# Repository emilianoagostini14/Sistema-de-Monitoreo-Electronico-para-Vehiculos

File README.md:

# Sistema-de-Monitoreo-Electronico-para-Vehiculos
Este repositorio contendrá los programas, archivos y diseños del proyecto integrador Sistema de Monitoreo Electronico  para Vehiculos

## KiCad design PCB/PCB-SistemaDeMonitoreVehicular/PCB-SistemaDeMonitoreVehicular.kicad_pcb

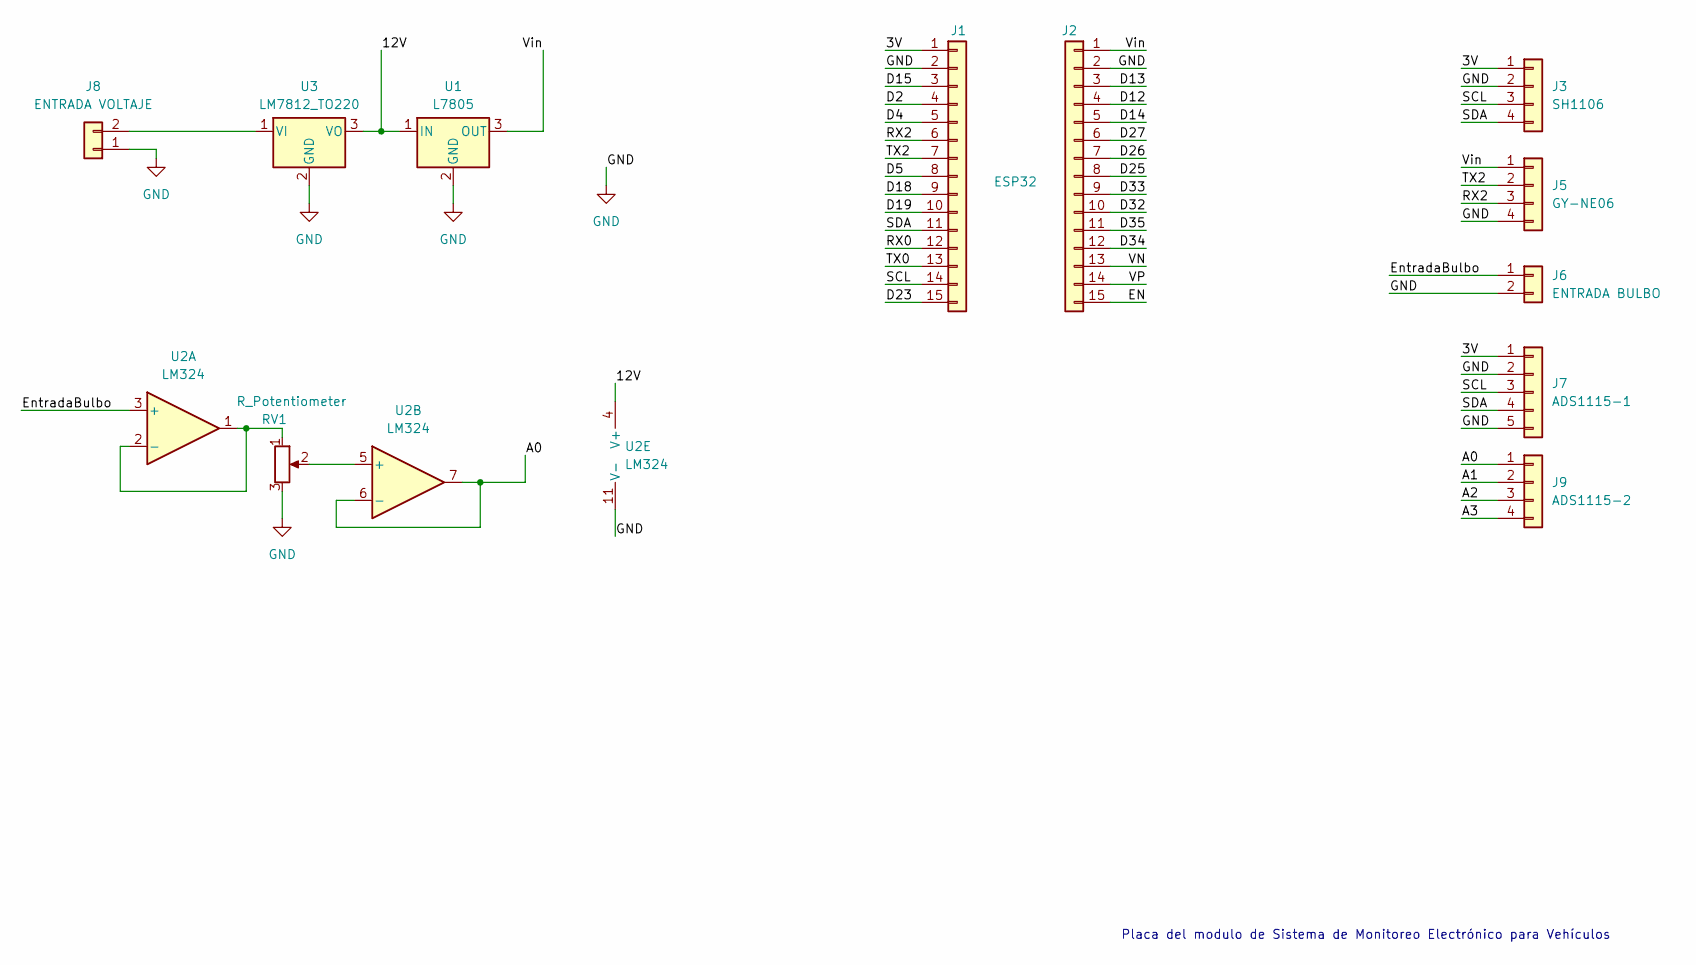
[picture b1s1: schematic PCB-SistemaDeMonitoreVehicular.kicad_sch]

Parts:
J1: ESP32; PinHeader_1x15_P2.54mm_Vertical
J2: Conn_01x15; PinHeader_1x15_P2.54mm_Vertical
J3: SH1106; PinHeader_1x04_P2.54mm_Vertical
J5: GY-NE06; PinHeader_1x04_P2.54mm_Vertical
J6: ENTRADA BULBO; TerminalBlock_bornier-2_P5.08mm
J7: ADS1115-1; PinHeader_1x05_P2.54mm_Vertical
J8: ENTRADA VOLTAJE; TerminalBlock_bornier-2_P5.08mm
J9: ADS1115-2; PinHeader_1x04_P2.54mm_Vertical
RV1: R_Potentiometer; Potentiometer_Bourns_3296W_Vertical
U1: L7805; TO-220-3_Vertical
U2: LM324; DIP-14_W10.16mm_LongPads
U3: LM7812_TO220; TO-220-3_Vertical

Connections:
/3V: J1.1, J3.1, J7.1
/12V: U1.1 (IN), U2.4 (V+), U3.3 (VO)
/A0: J9.1, U2.6 (-), U2.7
/A1: J9.2
/A2: J9.3
/A3: J9.4
/D2: J1.4
/D4: J1.5
/D5: J1.8
/D12: J2.4
/D13: J2.3
/D14: J2.5
/D15: J1.3
/D18: J1.9
/D19: J1.10
/D23: J1.15
/D25: J2.8
/D26: J2.7
/D27: J2.6
/D32: J2.10
/D33: J2.9
/D34: J2.12
/D35: J2.11
/EN: J2.15
/EntradaBulbo: J6.1, U2.3 (+)
/GND: J1.2, J2.2, J3.2, J5.4, J6.2, J7.2, J7.5, J8.1, RV1.3, U1.2 (GND), U2.11 (V-), U3.2 (GND)
/RX0: J1.12
/RX2: J1.6, J5.3
/SCL: J1.14, J3.3, J7.3
/SDA: J1.11, J3.4, J7.4
/TX0: J1.13
/TX2: J1.7, J5.2
/VN: J2.13
/VP: J2.14
/Vin: J2.1, J5.1, U1.3 (OUT)
unnamed: J8.2, U3.1 (VI)
unnamed: RV1.1, U2.1, U2.2 (-)
unnamed: RV1.2, U2.5 (+)

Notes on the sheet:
Placa del modulo de Sistema de Monitoreo Electrónico para Vehículos

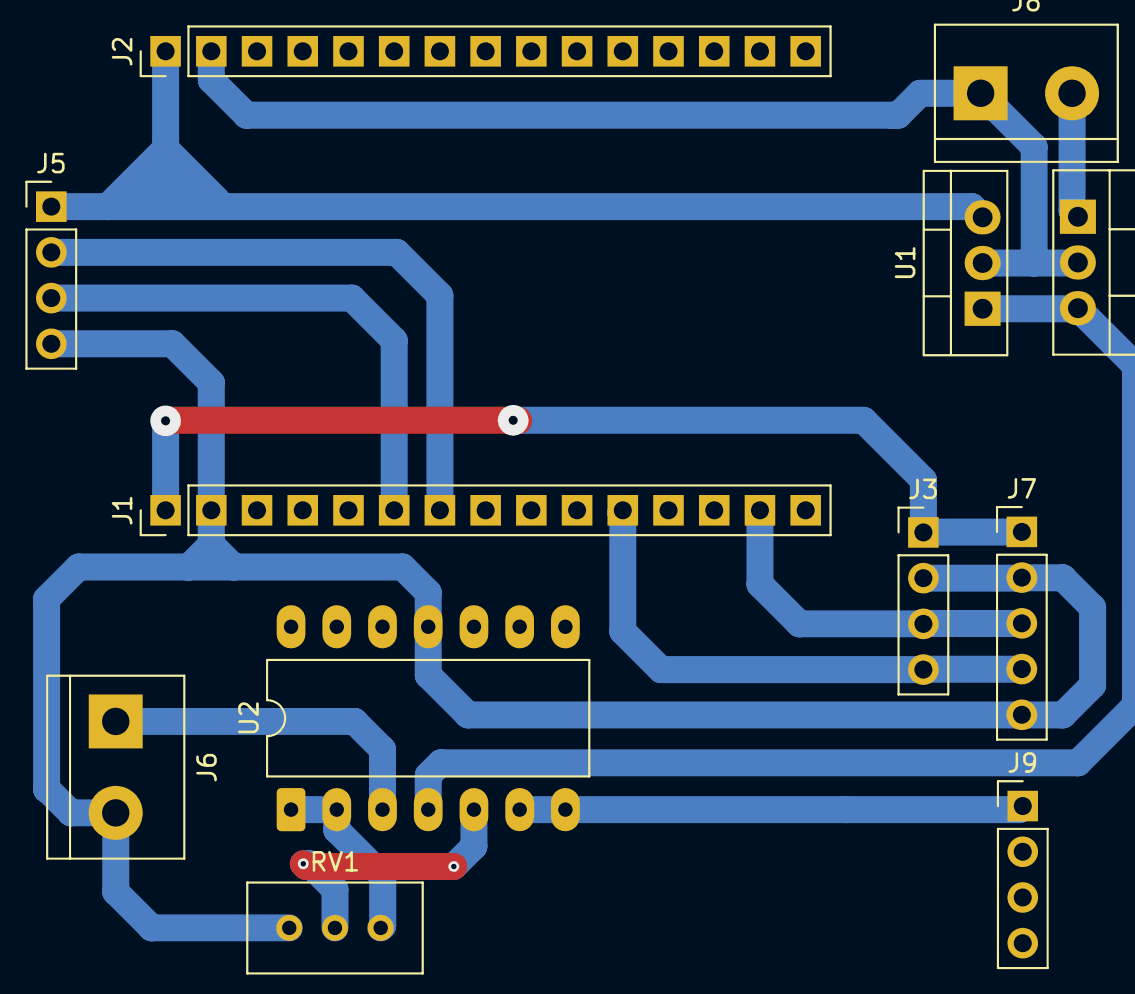
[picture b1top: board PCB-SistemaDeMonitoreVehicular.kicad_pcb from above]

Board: 2 copper layers, 12 parts (0 on the bottom side), 13 nets.

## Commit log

2025-11-07 ArchivosFinales
2025-11-10 Informe
2025-11-10 presentacion
